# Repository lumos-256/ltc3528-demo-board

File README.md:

# ltc3528-demo-board
Stepup switching regulator demo borad using LTC3528 IC

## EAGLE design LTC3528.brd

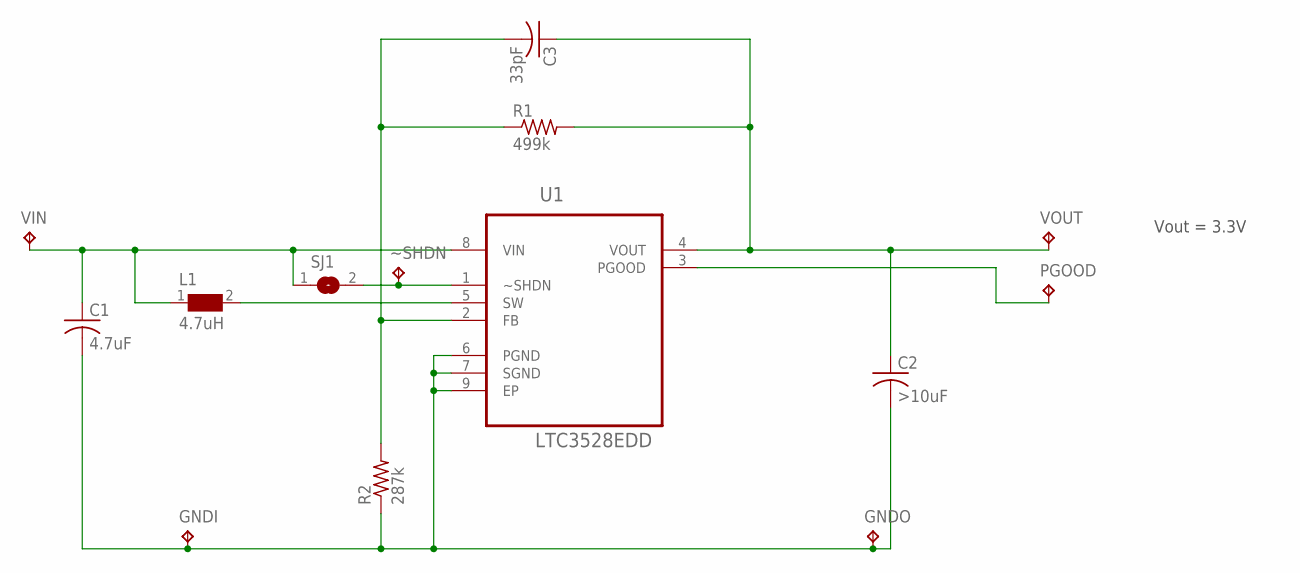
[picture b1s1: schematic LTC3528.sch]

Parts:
C1: 4.7uF; C0603
C2: >10uF; C0603
C3: 33pF; C0603
GNDI: TPPAD1-13; P1-13
GNDO: TPPAD1-13; P1-13
L1: 4.7uH; WE-TPC_2828
PGOOD: TPPAD1-13; P1-13
R1: 499k; R0603
R2: 287k; R0603
SJ1: not SHDN; SJ
U1: LTC3528EDD; DFN300X200X80-9N
VIN: TPPAD1-13; P1-13
VOUT: TPPAD1-13; P1-13
~SHDN: TPPAD1-13; P1-13

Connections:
GND: C1.2, C2.2, GNDI.TP, GNDO.TP, R2.1, U1.6 (PGND), U1.7 (SGND), U1.9 (EP)
unnamed: SJ1.2, U1.1 (~SHDN), ~SHDN.TP
unnamed: PGOOD.TP, U1.3 (PGOOD)
unnamed: L1.2, U1.5 (SW)
unnamed: C3.2, R1.1, R2.2, U1.2 (FB)
VIN: C1.1, L1.1, SJ1.1, U1.8 (VIN), VIN.TP
VOUT: C2.1, C3.1, R1.2, U1.4 (VOUT), VOUT.TP

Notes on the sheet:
Vout = 3.3V

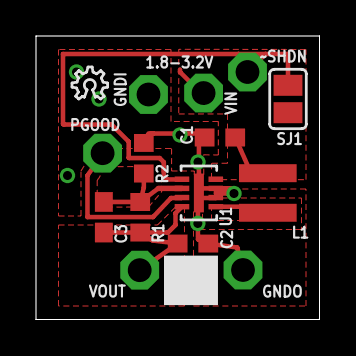
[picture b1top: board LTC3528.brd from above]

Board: 2 copper layers, 15.8 x 15.8 mm, 16 parts (1 on the bottom side), 7 nets.

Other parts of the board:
U$1: OSHW_6X70_NOTEXT
U$2: OSHW_6X100_NOTEXT

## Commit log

2016-03-27 V1.0 sent to OSHPark
2016-03-27 added images
2016-03-27 added LTC3528 datasheet
2016-03-27 some cleanup
2016-03-27 rm GPL LICENSE file

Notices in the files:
LTC3528.brd:
(c) 2016 Luc Chouinard
